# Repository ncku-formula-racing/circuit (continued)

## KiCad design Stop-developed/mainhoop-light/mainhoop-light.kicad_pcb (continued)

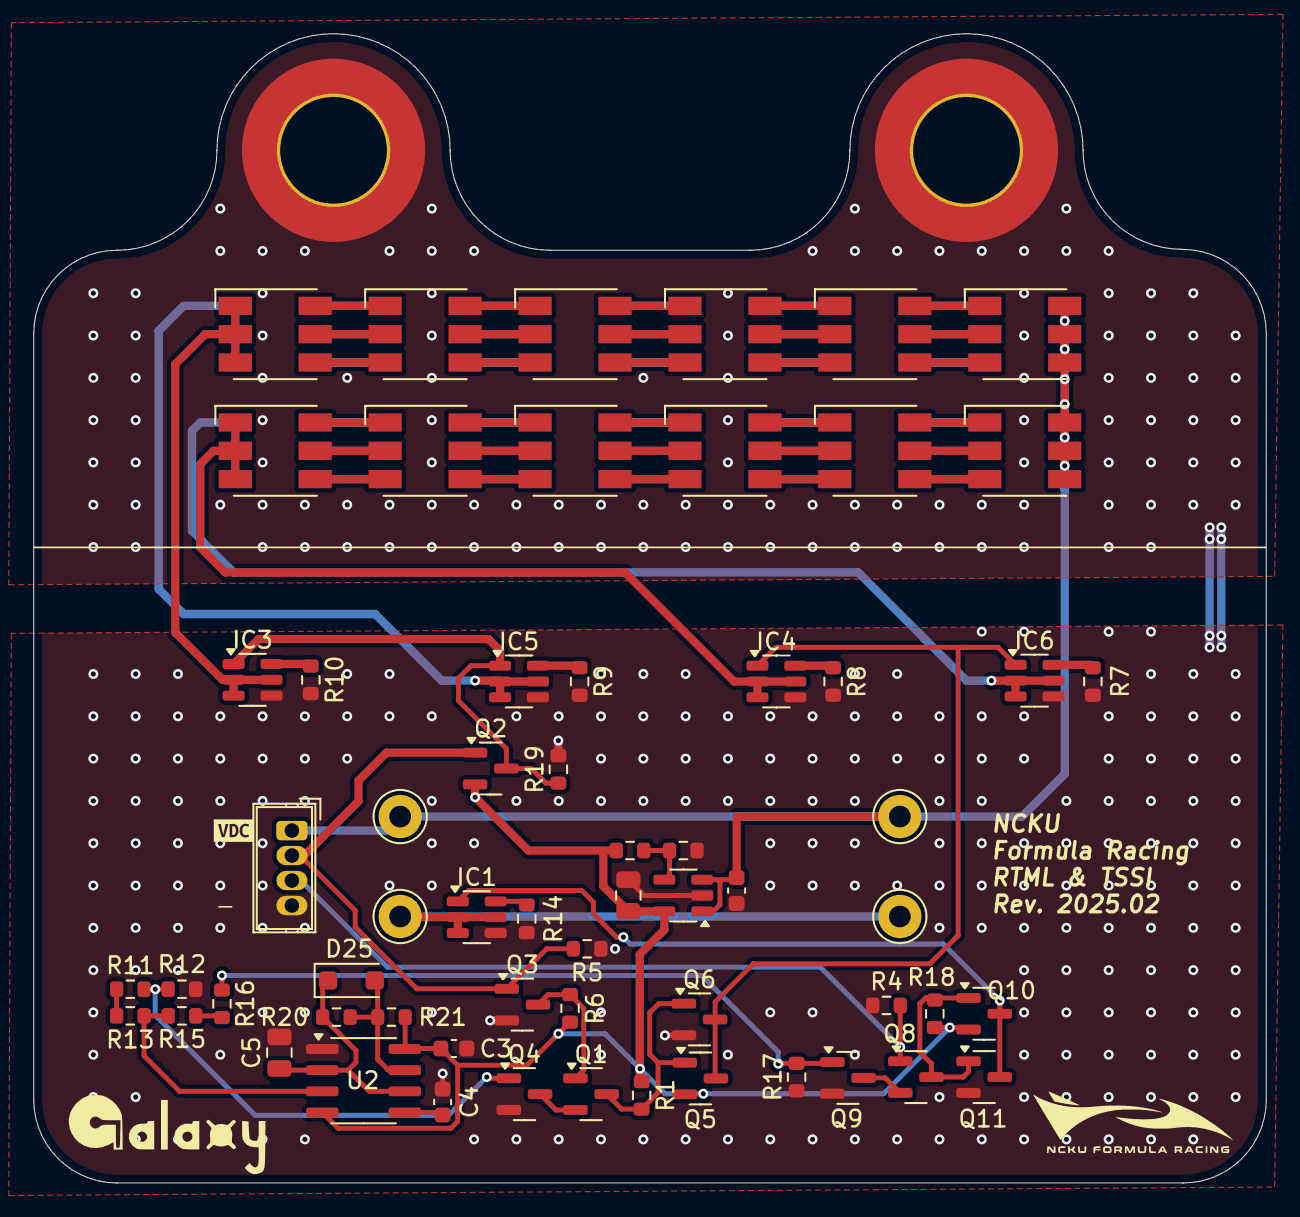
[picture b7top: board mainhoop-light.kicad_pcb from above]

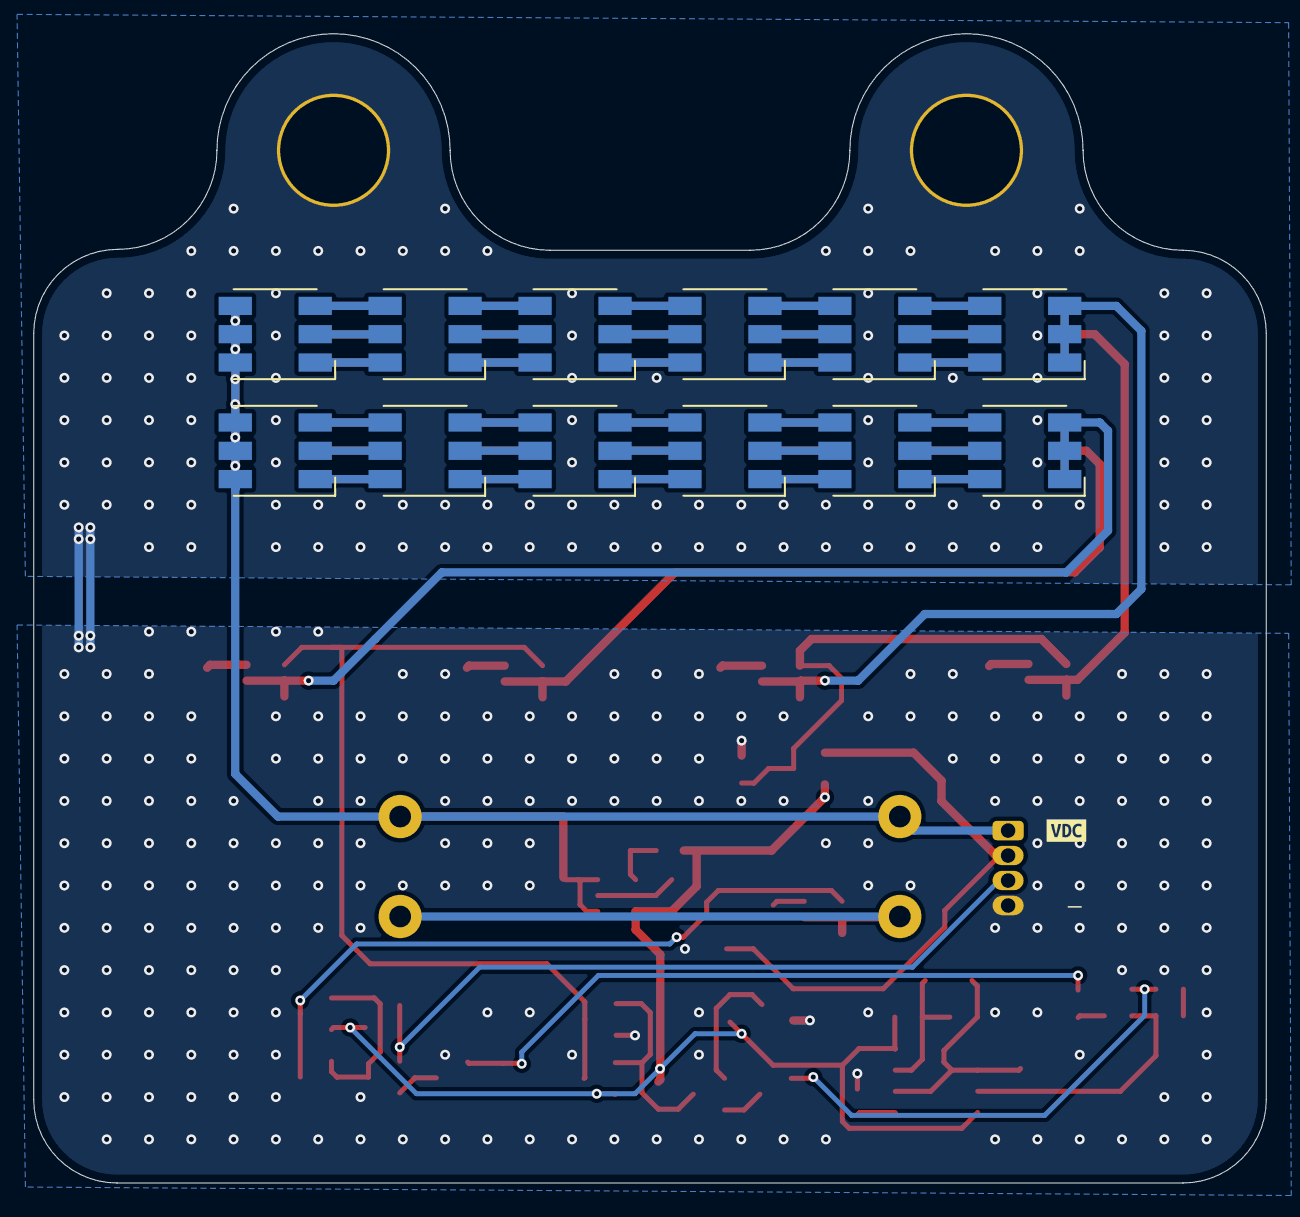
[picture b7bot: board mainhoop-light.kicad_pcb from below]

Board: 2 copper layers, 74.0 x 69.0 mm, 77 parts (13 on the bottom side), 92 nets.

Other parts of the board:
kibuzzard-67907CEC, kibuzzard-67907CEC#2: G***; kibuzzard-67907CEC

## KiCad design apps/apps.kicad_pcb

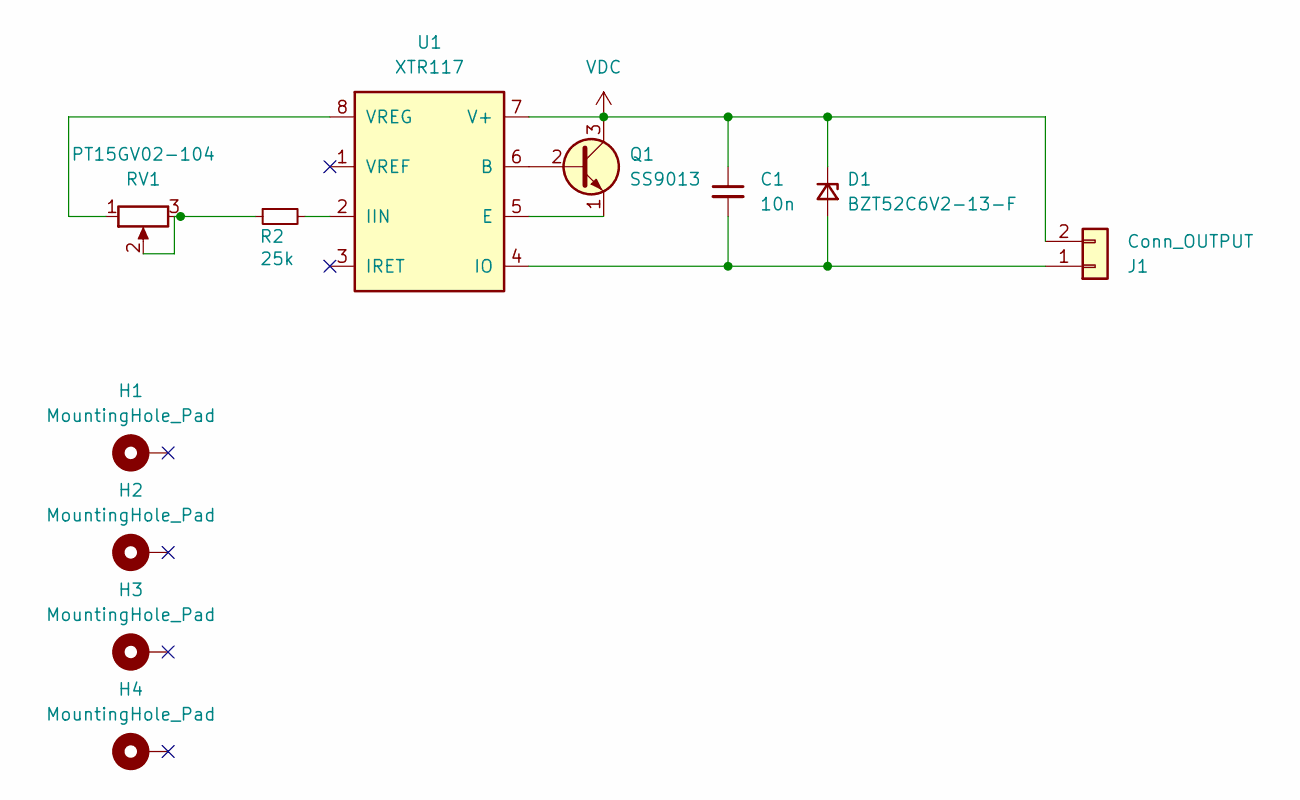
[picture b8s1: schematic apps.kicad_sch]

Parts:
C1: 10n; C_0603_1608Metric
D1: BZT52C6V2-13-F; D_SOD-123F
H1, H2, H3, H4: MountingHole_Pad; MountingHole_2.2mm_M2_Pad
J1: Conn_OUTPUT; JST_XH_B2B-XH-A_1x02_P2.50mm_Vertical
Q1: SS9013; SOT-23
R2: 25k; R_0603_1608Metric
RV1: PT15GV02-104; Potentiometer_Piher_PT-15-V02_Vertical_Hole
U1: XTR117; VSSOP-8_3.0x3.0mm_P0.65mm

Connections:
unnamed: C1.2, D1.2 (A), J1.1, U1.4 (IO)
unnamed: Q1.2 (B), U1.6 (B)
unnamed: Q1.1 (E), U1.5 (E)
unnamed: R2.1, RV1.2, RV1.3
unnamed: R2.2, U1.2 (IIN)
unnamed: RV1.1, U1.8 (VREG)
VDC: C1.1, D1.1 (K), J1.2, Q1.3 (C), U1.7 (V+)

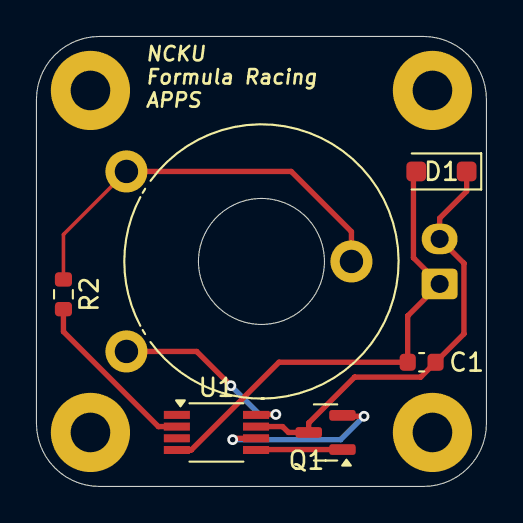
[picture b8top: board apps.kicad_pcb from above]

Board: 2 copper layers, 25.0 x 25.0 mm, 11 parts (1 on the bottom side), 7 nets.
